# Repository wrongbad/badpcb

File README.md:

# badpcb: an agent-facing PCB routing kernel

badpcb sits between an LLM (or a human) and PCB routing search. The agent makes the topological decisions (placement, pin assignment, corridors, which copper to unlock);
the kernel does the fast geometry and arithmetic and **always says why something is stuck**. No images are needed.

The idea
- **Named handles everywhere**: regions `R8`, cuts `C12`, conflict clusters `K1`, nets by name, parts by refdes. IDs are deterministic for the same geometry.
- **Text and matrix views**: `badpcb report` prints the crossing matrix, cut demand/capacity, an ASCII congestion map, feasibility of the design rules against fine-pitch footprints, lock classes and plane service. Every report has a JSON form.
- **What-if before commit**: small typed, reversible actions (`move`, `rot`, `flip`, `swap`, `assign`, `via`, `reshape`, `unlock`, hints...) in sessions with undo/snapshot/branch/diff. `badpcb eval` scores candidates (delta of crossings, overflow, wirelength...) without applying them.
- **Intent and floorplan**: `intent` in `badpcb.json` (soft near/apart/edge/clear/block constraints and reference layouts, scored as `intent=`), `badpcb floorplan` (blocks, fill, block-level crossings, what faces each fine-pitch IC side, long critical links).
- **Explanations**: `badpcb audit` (placement linter with ranked, legality-checked fixes; its header names the board file, its mtime and its zone count so a stale board is obvious; detectors ESCAPE, CHANNEL, PLANE, ROLES, INTENT, ...), `badpcb plan` (joint placement of an IC's fan-zone intruders and role parts), global router (`badpcb groute`, PathFinder with blockage history) and `badpcb droute` (scoped KiCadRoutingTools passes reported as open connections with region/cut handles and the locked copper that blocks them).
- **Net styles, route lint, polish**: `net_styles` in `badpcb.json` (soft per-net via penalty / detour budget / avoid / pair + skew / reference plane / priority, by name pattern or KiCad netclass), `badpcb styles` (resolved style per net), `badpcb lint` (per-net ugliness table: detour, vias, jogs, corners, direction breaks, plane splits, pair skew, escape-zone intrusions; weighted score, handle and reason per net), `droute --priority` (constrained nets first) and `droute --polish N` (rip and reroute the N worst nets, keep a result only if lint improves and open conns / DRC do not get worse).
- **No KiCad in the loop**: badpcb reads and edits `.kicad_pcb` files itself (pure stdlib S-expression editor: lossless, only the touched tokens change). KiCad is only the sign-off tool (`kicad-cli`: DRC, zone refill, fab output).

## Requirements
- Python 3.9+ (stdlib only; `numpy` optional).
- KiCad 8, 9 or 10 board files (tested on 10). `kicad-cli` is needed only for DRC / zone refill (`badpcb apply` verification); no `pcbnew`, no KiCad python.
- Optional, for `badpcb droute`: [KiCadRoutingTools](https://github.com/) (KRT) plus its own venv (numpy, scipy, shapely, Pillow; not KiCad's python).

## Install
```
pip install -e .            # console script `badpcb`
# or from a checkout, no install:
export PYTHONPATH=/path/to/badpcb-checkout      # then: python3 -m badpcb ...
source scripts/krt_env.sh                   # KRT_DIR / KRT_PY / KICAD_CLI defaults
```

## Environment variables
| var | meaning | default |
|---|---|---|
| `KICAD_CLI` | kicad-cli | `kicad-cli` on PATH, else the macOS app bundle |
| `KRT_DIR` / `KRT_PY` | KiCadRoutingTools checkout / its python | `badpcb.json` `krt`, else `~/KiCadRoutingTools` and `~/KiCadRoutingTools/.venv/bin/python` |
| `BADPCB_PROJECT` | badpcb.json (or its directory) | badpcb.json in the cwd or a parent |
| `BADPCB_HOME` | state directory (sessions, work files, cache) | `<project dir>/.badpcb/` |
| `BADPCB_NO_CACHE`, `BADPCB_GSCORE_CELL`, `BADPCB_PROGRESS_S` | disable groute cache / groute-score cell mm / droute progress seconds | |

State never goes into the package: `.badpcb/sessions`, `.badpcb/cache` (extracted models) and **`.badpcb/work/`**, the nested work directory for every intermediate artifact:
```
.badpcb/work/droute/<session|board>/passN.kicad_pcb, passN.krt.log/.json, passN.strip|repair|fanout.kicad_pcb, current.kicad_pcb, passes.jsonl
.badpcb/work/apply/<out board stem>/plan.json, apply_report.json, drc_in.json, drc.json
.badpcb/work/stubs/<out board stem>/   .badpcb/work/drc/   .badpcb/work/extract/
```
Only what you ask for lands elsewhere: the board named in `apply S out.kicad_pcb` / `droute --out` / `stubs in out` (with its `.kicad_pro`/`.kicad_dru`) and `swaps_applied.md` beside it. The directory is configurable (`"work_dir": "build/work"` in `badpcb.json`, relative to the project) so the project top level keeps only the final board, the config, notes and `fab/`.

## Project config: `badpcb.json`
Found in the cwd (or a parent), via `--project PATH`, or `$BADPCB_PROJECT`. All keys optional; relative paths are relative to the file. Without one badpcb auto-detects fine-pitch parts and has no swap groups or lock classes.
```json
{
  "board": "my_board.kicad_pcb",
  "rules": {"project": "my_board.kicad_pro"},
  "mcu": "U1",
  "fine_pitch_parts": ["U1"],
  "swaps": "swaps.json",
  "locks": {"classes": {"lane": {"file": "lanes.json", "protect": true, "trim": true},
                        "mimic": {"file": "mimic.json", "key": "copied"}},
            "trim": {"nets": "^(EN|SENSE)\\d+$", "key_parts": "^U1\\d\\d$", "start_part": "U1"}},
  "audit": {"decap_bypass_mm": 4.0},
  "planes": {"assume": ["GND", "+3V3"], "min_coverage": 0.30},
  "work_dir": ".badpcb/work",
  "intent": {"blocks": {"vreg": {"parts": ["L1", "C15", "C17"], "max_span_mm": 10}},
             "near": [["decaps:U1", "U1", 3]], "clear": [{"zone": "escape:U1", "except": ["decaps:U1"]}], "edge": [["J1", "back", 2]]},
  "krt": {"dir": "../tools/KiCadRoutingTools", "python": "../tools/krt-venv/bin/python"}
}
```
- `rules.project`: the `.kicad_pro` (+ sibling `.kicad_dru`) DRC is graded against and copied beside every board badpcb writes (default: the input board's own).
- `mcu`, `fine_pitch_parts`: the IC pin-swap groups apply to / parts whose fan-out matters (default: auto-detect pitch < 0.65 mm).
- `swaps`: file or inline dict `{"mcu", "pin_names": {pin: name}, "groups": [...]}`; group kinds `pin_permutation`, `pin_assignment`, `part_sets`, `key_assignment` (needs `net_regex`). See `examples/pcb_v2/swaps.json`.
- `locks.classes`: copper lock classes, none by default. Each is `"name": "file[:key]"` (JSON list of track/via uuids, or `d[key]`) or `{"file", "key", "protect", "trim"}`. `protect`: `apply` keeps the copper unless a changed pad shorts or breaks it, and `legal`/`stubs` treat it as hard copper. `trim`: eligible for `trim [CLASS]` (alias `trim-lanes`; all trim classes when no CLASS); it may be a dict that overrides `locks.trim` (`nets`, `key_parts`, `start_part`, `band_depth`) for that class. Output labels use the class name.
- `audit`: overrides for the ROLES / escape-zone thresholds (decap, filter-cap, crystal, pull-up distances, slack factors, minimum IC pins, fan-zone depth, joint-placement limits). Defaults and meanings: `DEFAULTS` in `badpcb/audit.py`; unknown keys are rejected. `badpcb audit --roles` and `badpcb project` print the effective values.
- `planes.assume`: nets treated as plane nets on boards with no zones yet. `planes.min_coverage` (default 0.30): a layer is a **plane layer** only when its netted zones (outlines, so unfilled zones count) cover more than this fraction of the board outline; a few-mm2 outer-layer pour (regulator LX / +1V1) does not make the layer a plane, so droute keeps routing on it. `report --section summary` and every `droute` pass print which zones made each decision (`0` = any netted zone, the old behaviour).
- `work_dir`: nested work directory for intermediates (default `<state dir>/work`, see above).
- `intent`: soft design intent, an inline object or the path of a JSON file; see **Design intent** below.
`badpcb project` prints what was resolved (`no lock classes` when there is no `locks` block; lock files that do not exist are flagged, not fatal).

## Design intent (`intent`)
What the placement should look like, as **soft penalties only**: no vetoes, no rigid locks. A broken intent just costs and is reported;
breaking a reference on purpose is allowed, it has to be visible. The sum of all weighted penalties is the `intent` metric: `intent=N` in the
session METRICS line (only when intent is declared; without intent every METRICS line is exactly as before), a term of every `dscore`
(`eval`, `suggest`, audit fix ranking, `plan`), and `0` means every intent is met. Selectors in all entries: a refdes, a glob (`C1*`, `U1??`),
comma lists, or a role `decaps:U1` (supply caps <= 1.5 uF whose nearest IC pin on their net is on U1), `bulk:U1`, `caps:U1`, `passives:U1`.
Distances are courtyard-box gaps (box to box, or box to a pad point); every entry takes an optional `weight` (last list element, or `"weight"`).
```json
"intent": {
  "refs": {"mini": {"pcb": "../ref/minimal/board.kicad_pcb", "anchor": "U1"}},
  "blocks": {"vreg":  {"parts": ["L1", "C15", "C16", "C17", "R3"], "max_span_mm": 10, "anchor": "U1",
                       "ref": {"pcb": "../ref/minimal/board.kicad_pcb", "anchor": "U1", "map": {"C15": "C6"}}},
             "flash": {"parts": ["U2"], "ref": "mini"}},
  "near":  [["decaps:U1", "U1", 3], ["Y1", "U1.20", 6, 2.0]],
  "apart": [["J1", "U1", 8]],
  "edge":  [["J1", "back", 2], ["J2", "any"]],
  "clear": [{"zone": "escape:U1", "except": ["decaps:U1"], "weight": 3}, {"zone": [10, 5, 40, 20]}]
}
```
| entry | meaning | penalty (x weight) |
|---|---|---|
| `blocks: {name: {parts, max_span_mm?, anchor?, ref?}}` | parts that belong together (also the floorplan's declared blocks) | span: `0.5` per mm of centre-bbox diagonal over `max_span_mm`; reference drift: `0.3` per mm above 1 mm (below) |
| `near: [A, B[.PAD], mm]` | each part of A within `mm` (gap) of part B or its pad | per mm of excess (default weight 1) |
| `apart: [A, B, mm]` | at least `mm` between every A and B | per mm of shortfall (1) |
| `edge: [REF, front\|back\|left\|right\|any, max_mm?]` | courtyard within `max_mm` (default 3) of that board edge; front = +Y (bottom), back = top | per mm over (0.5) |
| `clear: {zone, except?}` | nothing in the zone but the excepted parts; `zone` = `escape:U1[:N]` (the fan zones of an IC, optionally one side) or a box `[x0, y0, x1, y1]` | per intruder `1 + min(overlap mm2, 25) / 5` (2) |
- **Reference blocks**: `ref` = a reference `.kicad_pcb` path or a name from `refs`, `{pcb, anchor, map}` (`map`: `{part here: part there}` for parts whose
  refdes differ; the anchor is an IC present in both boards, may be outside the block), or a captured arrangement (below). Alignment is the best
  rigid fit (rotation, translation, mirror when the board sides differ) of the anchor's pads by pad number, so the reference may be on the other
  board side or turned. **Drift** = RMS of the members' offsets from where the reference puts them + `0.25 mm` per member turned by 90 degrees
  (mod 180); a drift above 1 mm costs `0.3 x weight` per mm and is listed in the audit and the floorplan.
- In a session: `badpcb act S 'intent add {"near": ["C5", "U1.5", 3]}'` (same JSON as the config sections, singular or plural), `'intent rm near2 block:vreg'`
  (ids as shown by `badpcb show S`: `near1`, `edge2`, `clear1`, `block:vreg`), `'intent capture vreg'` (the block's reference := the current positions of its parts
  relative to the anchor). All are logged, undoable and part of `snapshot`/`branch` like hints. Entries from `badpcb.json` can be removed the same way.
- `badpcb audit S --only INTENT`: one finding per violated entry (WARN; ERR once the weighted penalty reaches `audit.intent_err`, default 8), with
  compact fixes and their delta; unresolved selectors are NOTEs. `badpcb plan` adds 0.5 x the intent penalty of a candidate spot to its cost.
- `examples/pcb_v2/badpcb.json` has an intent for the case-study board (blocks mcu / vreg / flash / xtal from the RP2350 minimal design).

## Net styles, route lint and polish
```json
"net_styles": {
  "usb_d":   {"match": ["USB_D*"], "pair": "USB_DP/USB_DN", "skew_mm": 0.5, "via_penalty": 8, "keep_ref_plane": true, "priority": true},
  "vreg_lx": {"match": ["VREG_LX"], "via_penalty": 6, "detour_max": 1.3, "avoid": ["XIN", "XOUT", "ADC*"], "priority": true},
  "power":   {"class": "Power", "via_penalty": 2}
}
```
Keys: `match` (fnmatch globs / exact names), `class` (a KiCad netclass; read from the board's `.kicad_pro`: `net_settings.netclass_assignments` and `netclass_patterns`), `via_penalty` (extra via cost, mm of path like groute's `--via-cost`),
`detour_max` (routed / direct length the net should stay under), `avoid` (net globs to keep away from), `pair` (`"P/N"`), `skew_mm`, `keep_ref_plane`, `priority`. A net gets a style by name **or** netclass; when several styles match they **stack** and the stricter value per key wins
(max `via_penalty`, min `detour_max` / `skew_mm`, union of `avoid` / pairs, OR of the flags). Everything is soft: penalties and ranking, never a veto. No `net_styles` = nothing changes.
- `badpcb styles BOARD [--json]`: the resolved style per net (and styles that matched nothing, and the nets the priority pass will take).
- **groute** uses them per net: via cost = base + `via_penalty`, a tight `detour_max` weights path length up, `avoid` is a soft proximity cost around the other nets' copper (mutual).
- `badpcb lint BOARD [--nets GLOB ..] [--top N] [--all] [--json]` (also `report --section lint`): for every routed signal net (plane nets, stitching vias and single-pad nets excluded) detour ratio, signal vias, jogs (segment < 3 x track width between two bends), bends per 10 mm, acute and 90 degree corners, layer-direction breaks (each layer's dominant direction is inferred from its copper),
  tracks over a split or gap of the adjacent reference plane (outer layers vs the zone outlines of the plane layer next to them), pair skew / gap variation / uncoupled share, copper inside another fine-pitch part's escape zone, copper close to `avoid` nets. A weighted score per net (`DEFAULTS` in `badpcb/lint.py`, `"lint": {"weights": {...}}` in `badpcb.json`; the style scales it:
  `via_penalty` -> via weight, `keep_ref_plane` -> splits x3, `priority` -> x1.5), a table sorted worst first with the reason and a handle (`C12` / `U1-in` / `R8`), the board total, and a verdict: few bad nets -> candidates for polish, many -> ESCALATE (placement problem).
- `badpcb droute BOARD --priority [--clean-board] [--strip]`: constrained-first pass for the nets with `priority`, `via_penalty >= 8` or a `pair`. KRT has one via cost per run (no per-net option, `route.py --via-cost`), so the pass routes those nets alone with the strictest via cost (75 + 10 x via_penalty), `--turn-cost 1500` and `--keep-away` bands for `avoid`
  (KRT also has `route_diff.py` for differential pairs; not wired in). A normal pass raises the via cost only if every net of its scope has a `via_penalty`.
- `badpcb droute BOARD --polish N [--time S] [--out BOARD]`: on a routed board rip and reroute the N worst nets of the lint (a pair together), one at a time, rest frozen (`--keep-input-copper`, KRT's pre-existing-rip disabled); a candidate is kept only if open connections, DRC errors and unconnected items do not increase, no other net's copper changed and the net's lint score improved. `--time` is the total budget. Logged per net with before/after.

## Quickstart
```
cd my_board_dir                          # holds badpcb.json
badpcb report my_board.kicad_pcb             # feasibility, summary, clusters, copper, cuts, planes, mcu, map
badpcb session new s1 my_board.kicad_pcb
badpcb floorplan s1                          # blocks, connectors, what faces the MCU fan, long links
badpcb audit s1                              # placement findings with fixes (incl. INTENT)
badpcb eval s1 'move R20 153.4 1.1' 'rot C27 90'
badpcb act s1 'move R20 153.4 1.1'
badpcb groute s1 --region R8 --time 20
badpcb apply s1 out.kicad_pcb                # writes the board, verifies metrics + DRC
badpcb droute s1 --region R8 --fanout U1     # needs KiCadRoutingTools
badpcb droute out.kicad_pcb --measure        # METRICS line (badpcb + DRC)
```

## Command reference
`report` `lint` `styles` `session new|ls|rm` `act` `eval` `suggest` `audit` `plan` `floorplan` `groute` `undo` `snapshot` `revert` `branch` `switch` `diff` `log` `spots` `show` `apply` `droute` `project`. `badpcb <cmd> -h` lists options; action syntax is in the docstring of `badpcb/actions.py`.

## Typical agent loop
Get the start right, then route: `0 simplify the architecture -> 1 reference first (intents + reference blocks) -> 2 floorplan (blocks before parts) -> 3 draft placement inside the blocks -> 4 gate (audit + intent) -> 5 route in scoped passes -> 6 escalate upward (re-floorplan) instead of patching`.
Steps 4-5 are the inner loop `report -> feasibility -> audit -> small fix -> groute score -> scoped droute -> repair -> audit`; more than ~2 repair passes in a region, or the ping-pong warning, means going back to step 2/3. Full version: [docs/PLAYBOOK.md](docs/PLAYBOOK.md). Design: [docs/ARCHITECTURE.md](docs/ARCHITECTURE.md). Case study: [docs/HISTORY.md](docs/HISTORY.md), [examples/pcb_v2](examples/pcb_v2) (steered routing of the first board), [examples/pcb_v4](examples/pcb_v4) (the start-right respin, with example `net_styles`).

## Using badpcb from a board project
Keep the board repo free of kernel code: put `badpcb.json` (+ swaps and lock files) next to the board, `export PYTHONPATH=/path/to/badpcb` (or `pip install -e`), run from the board directory. State lands in the board's `.badpcb/`. Board-specific tests go in the board project and run against the shared package (`PYTHONPATH=../badpcb python3 -m unittest discover -s rk_board_tests -t .`).

## Tests
`python3 -m unittest discover -s tests -t .` (synthetic, no KiCad needed; the parser/writer tests use the small boards in `tests/fixtures/`, and one test is skipped unless `kicad-cli` is installed). `tests/test_board_smoke.py` is skipped unless `BADPCB_TEST_BOARD=/path/board.kicad_pcb`.

## License

Mozilla Public License 2.0 (see `LICENSE`). Use badpcb for anything, including commercial work; designs you make with it are yours. If you distribute modified badpcb files, share those changes under MPL-2.0. Contributions are welcome, see `CONTRIBUTING.md`.

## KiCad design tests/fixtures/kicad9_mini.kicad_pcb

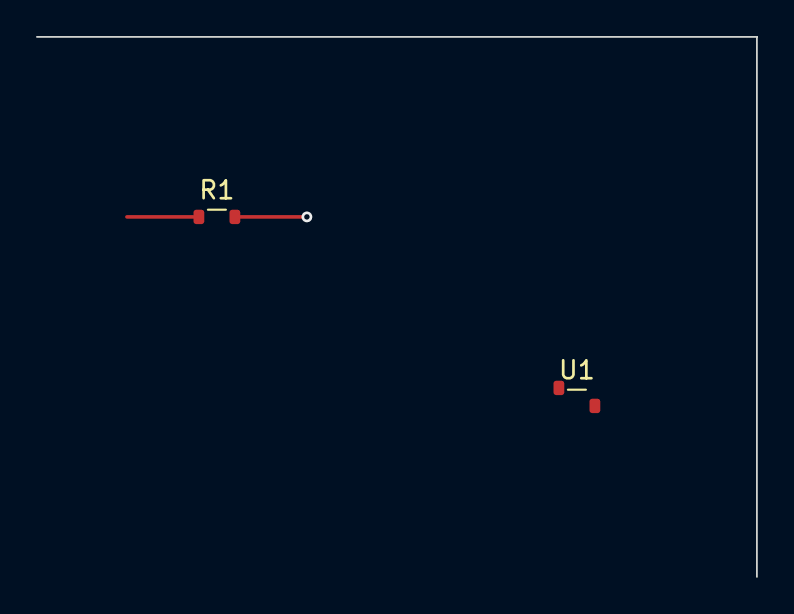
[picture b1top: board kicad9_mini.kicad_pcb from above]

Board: 4 copper layers, 40.0 x 30.0 mm, 3 parts (1 on the bottom side), 2 nets.

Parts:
C1: 100n; C_0402
R1: 10k; R_0603
U1: IC; SOT_DUAL

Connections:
A: R1.1, U1.1
B: C1.1, R1.2, U1.2
